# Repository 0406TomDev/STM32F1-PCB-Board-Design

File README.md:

# STM32F1-PCB-Board-Design
 This is my second PCB design. In this project , I use Kicad to design the Board of STM32F103C8T6.
 I have uploaded my design to https://www.jlcpcb.com so you can reference and order it.

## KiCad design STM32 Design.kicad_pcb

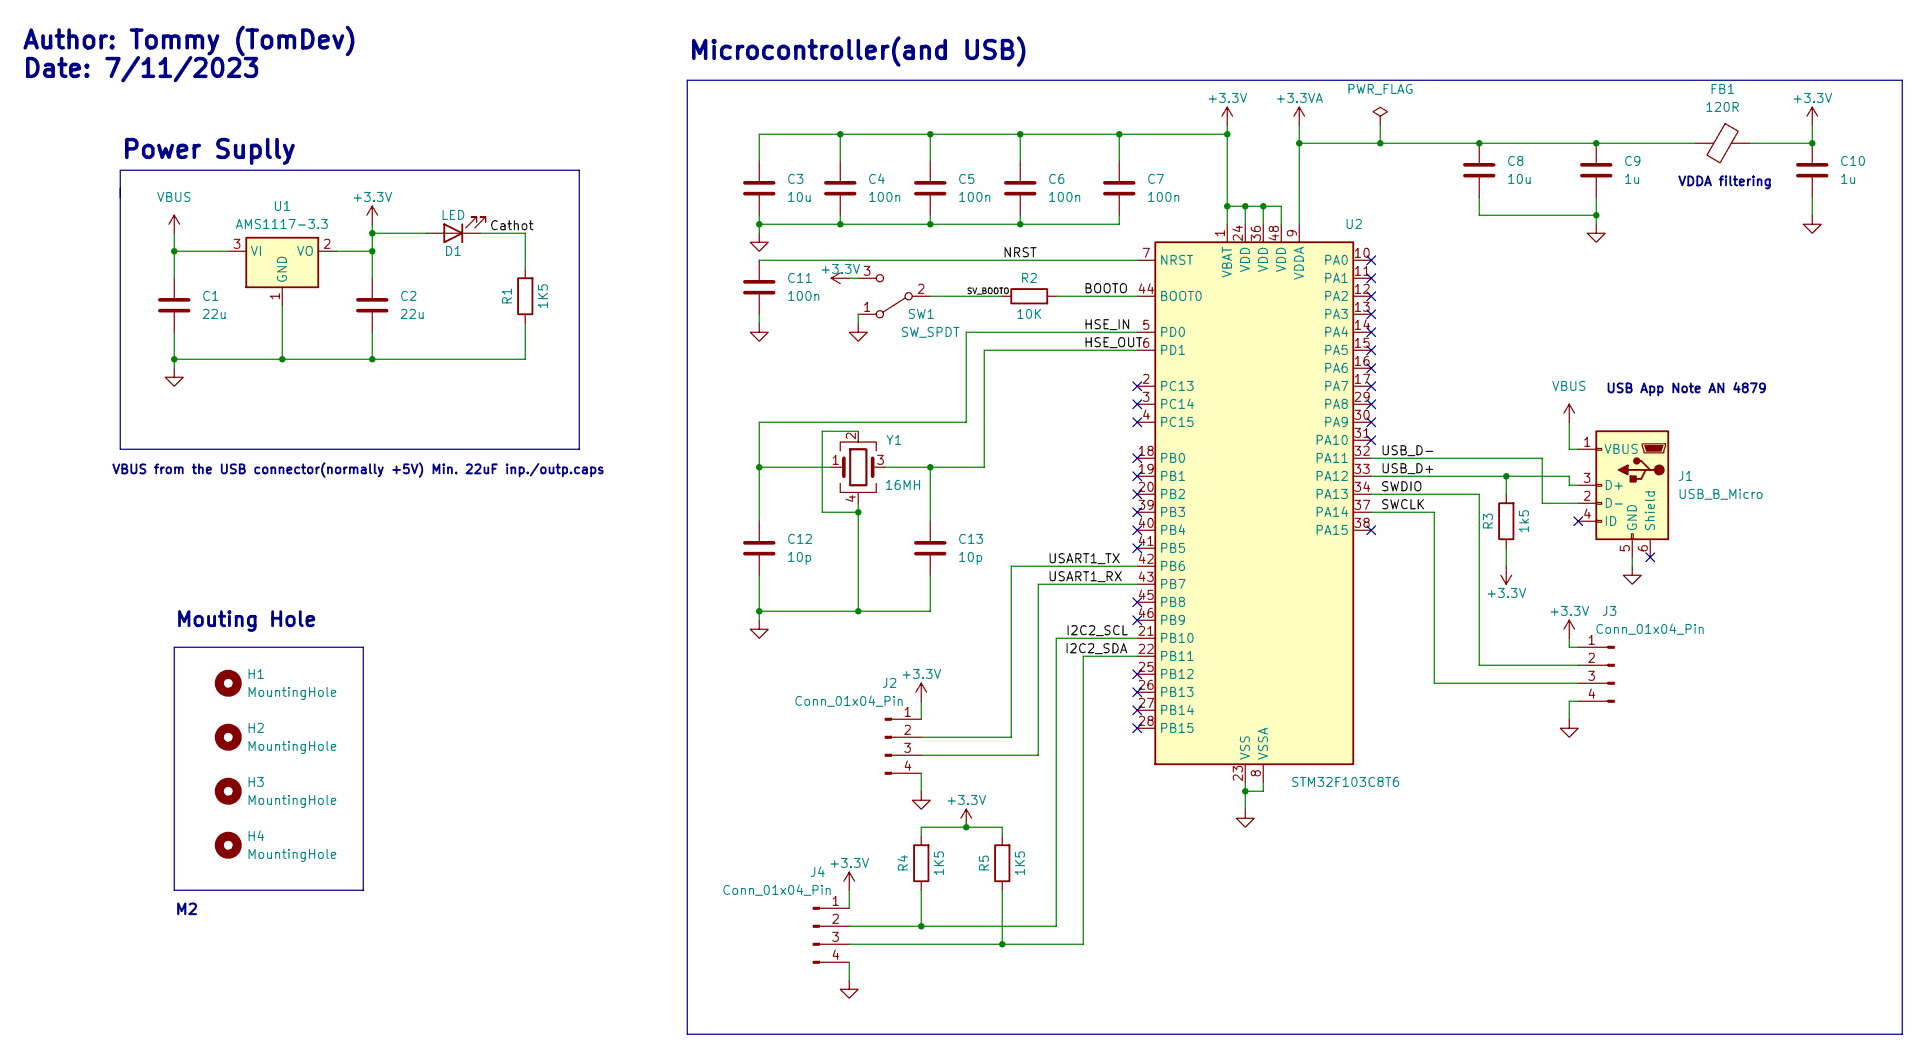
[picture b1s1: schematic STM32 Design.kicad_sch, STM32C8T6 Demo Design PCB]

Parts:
C1, C2: 22u; C_0805_2012Metric
C3: 10u; C_0603_1608Metric
C4, C5, C6, C7, C11: 100n; C_0402_1005Metric
C8: 10u; C_0402_1005Metric
C9, C10: 1u; C_0402_1005Metric
C12, C13: 10p; C_0402_1005Metric
D1: LED; LED_0603_1608Metric
FB1: 120R; L_0603_1608Metric
H1, H2, H3, H4: MountingHole; MountingHole_2.2mm_M2
J1: USB_B_Micro; USB_Micro-B_Wuerth_629105150521
J2, J3, J4: Conn_01x04_Pin; PinHeader_1x04_P2.54mm_Vertical
R1, R4, R5: 1K5; R_0402_1005Metric
R2: 10K; R_0402_1005Metric
R3: 1k5; R_0402_1005Metric
SW1: SW_SPDT; SW_SPDT_PCM12
U1: AMS1117-3.3; SOT-223-3_TabPin2
U2: STM32F103C8T6; LQFP-48_7x7mm_P0.5mm
Y1: 16MH; Crystal_SMD_3225-4Pin_3.2x2.5mm

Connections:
+3.3V: C2.1, C3.1, C4.1, C5.1, C6.1, C7.1, C10.1, D1.2 (A), FB1.1, J2.1, J3.1, J4.1, R3.1, R4.2, R5.2, SW1.3 (C), U1.2 (VO), U2.1 (VBAT), U2.24 (VDD), U2.36 (VDD), U2.48 (VDD)
+3.3VA: C8.1, C9.1, FB1.2, U2.9 (VDDA)
/BOOTO: R2.2, U2.44 (BOOT0)
/Cathot: D1.1 (K), R1.2
/HSE_IN: C12.1, U2.5 (PD0), Y1.1
/HSE_OUT: C13.1, U2.6 (PD1), Y1.3
/I2C2_SCL: J4.2, R4.1, U2.21 (PB10)
/I2C2_SDA: J4.3, R5.1, U2.22 (PB11)
/NRST: C11.1, U2.7 (NRST)
/SV_BOOTO: R2.1, SW1.2 (B)
/SWCLK: J3.3, U2.37 (PA14)
/SWDIO: J3.2, U2.34 (PA13)
/USART1_RX: J2.3, U2.43 (PB7)
/USART1_TX: J2.2, U2.42 (PB6)
/USB_D+: J1.3 (D+), R3.2, U2.33 (PA12)
/USB_D-: J1.2 (D-), U2.32 (PA11)
GND: C1.2, C2.2, C3.2, C4.2, C5.2, C6.2, C7.2, C8.2, C9.2, C10.2, C11.2, C12.2, C13.2, J1.5 (GND), J2.4, J3.4, J4.4, R1.1, SW1.1 (A), U1.1 (GND), U2.8 (VSSA), U2.23 (VSS), U2.35 (VSS), U2.47 (VSS), Y1.2, Y1.4
VBUS: C1.1, J1.1 (VBUS), U1.3 (VI)

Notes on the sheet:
VBUS from the USB connector(normally +5V) Min. 22uF inp./outp.caps
Mouting Hole
USB App Note AN 4879
VDDA filtering
Power Suplly
Author: Tommy (TomDev) Date: 7/11/2023
Microcontroller(and USB)

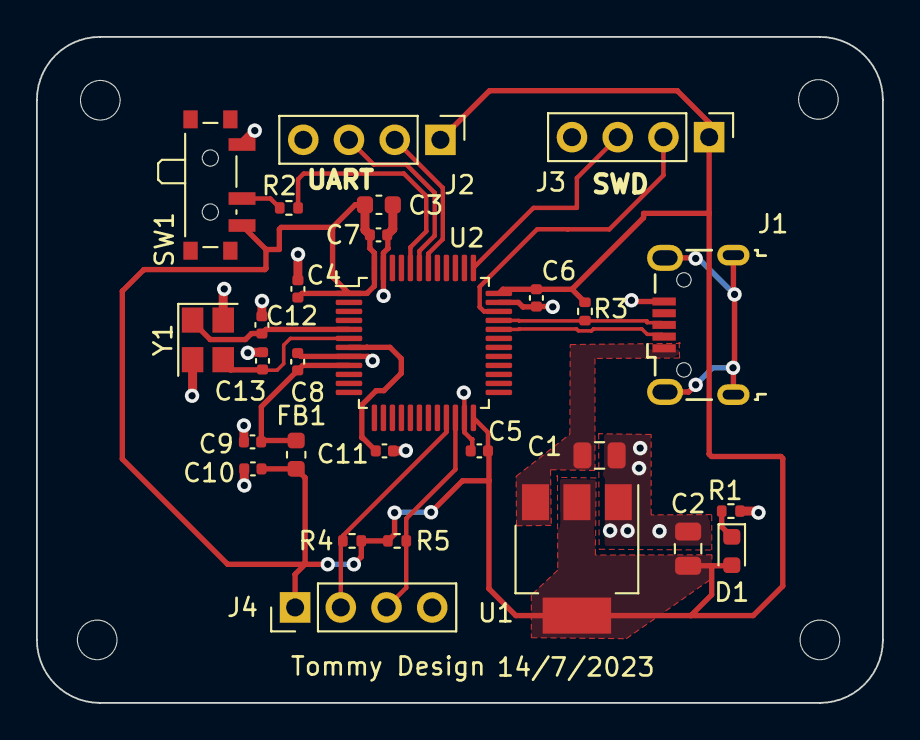
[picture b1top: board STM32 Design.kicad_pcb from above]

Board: 2 copper layers, 47.0 x 37.0 mm, 32 parts (0 on the bottom side), 18 nets.
